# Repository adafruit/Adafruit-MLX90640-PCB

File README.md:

## Adafruit MLX90640 IR Thermal Camera Breakout PCB

<a href="http://www.adafruit.com/products/4407"><br/>
Click here to purchase one from the Adafruit shop</a><br/>
<a href="http://www.adafruit.com/products/4469"><br/>
Click here to purchase one from the Adafruit shop</a>

PCB files for the Adafruit MLX90640 IR Thermal Camera Breakout. 

Format is EagleCAD schematic and board layout
* https://www.adafruit.com/product/4407
* https://www.adafruit.com/product/4469

### Description

You can now add affordable heat-vision to your project and with an Adafruit MLX90640 Thermal Camera Breakout. This sensor contains a 24x32 array of IR thermal sensors. When connected to your microcontroller (or Raspberry Pi) it will return an array of 768 individual infrared temperature readings over I2C. It's like those fancy thermal cameras, but compact and simple enough for easy integration.

One version has a narrow 55°x35° field of view, and we also have a version with a wider 110°x70° field of view

This part will measure temperatures ranging from -40°C to 300°C with an accuracy of +- 2°C (in the 0-100°C range). With a maximum frame rate of 16 Hz (the theoretical limit is 32Hz but we were not able to practically achieve it), It's perfect for creating your own human detector or mini thermal camera. We have code for using this sensor on an Arduino or compatible (the sensor communicates over I2C) or on a Raspberry Pi with Python. If using an Arduino-compatible, you'll need a processor with at least 20KB RAM - a SAMD21 (M0) or SAMD51 (M4) chipset will do nicely. On the Pi, you can even perform interpolation processing with help from the SciPy python library and get some pretty nice results!

This sensor reads the data twice per frame, in a checker-board pattern, so it's normal to see a checker-board dither effect when moving the sensor around - the effect isn't noticeable when things move slowly.

To make it easy to use, we hand-soldered it on a breakout board with a 3.3V regulator and level shifting. So you can use it with any 3V or 5V microcontroller or computer. We've even included SparkFun qwiic compatible STEMMA QT connectors for the I2C bus so you don't even need to solder! Just plug-n-play with any of our STEMMA QT (JST SH) cables.

Even better - We've done all the hard work here, with example code and supporting software libraries to get you up in running in just a few lines of Arduino or Python code

### License

Adafruit invests time and resources providing this open source design, please support Adafruit and open-source hardware by purchasing products from [Adafruit](https://www.adafruit.com)!

Designed by Limor Fried/Ladyada for Adafruit Industries.

Creative Commons Attribution/Share-Alike, all text above must be included in any redistribution. 
See license.txt for additional details.

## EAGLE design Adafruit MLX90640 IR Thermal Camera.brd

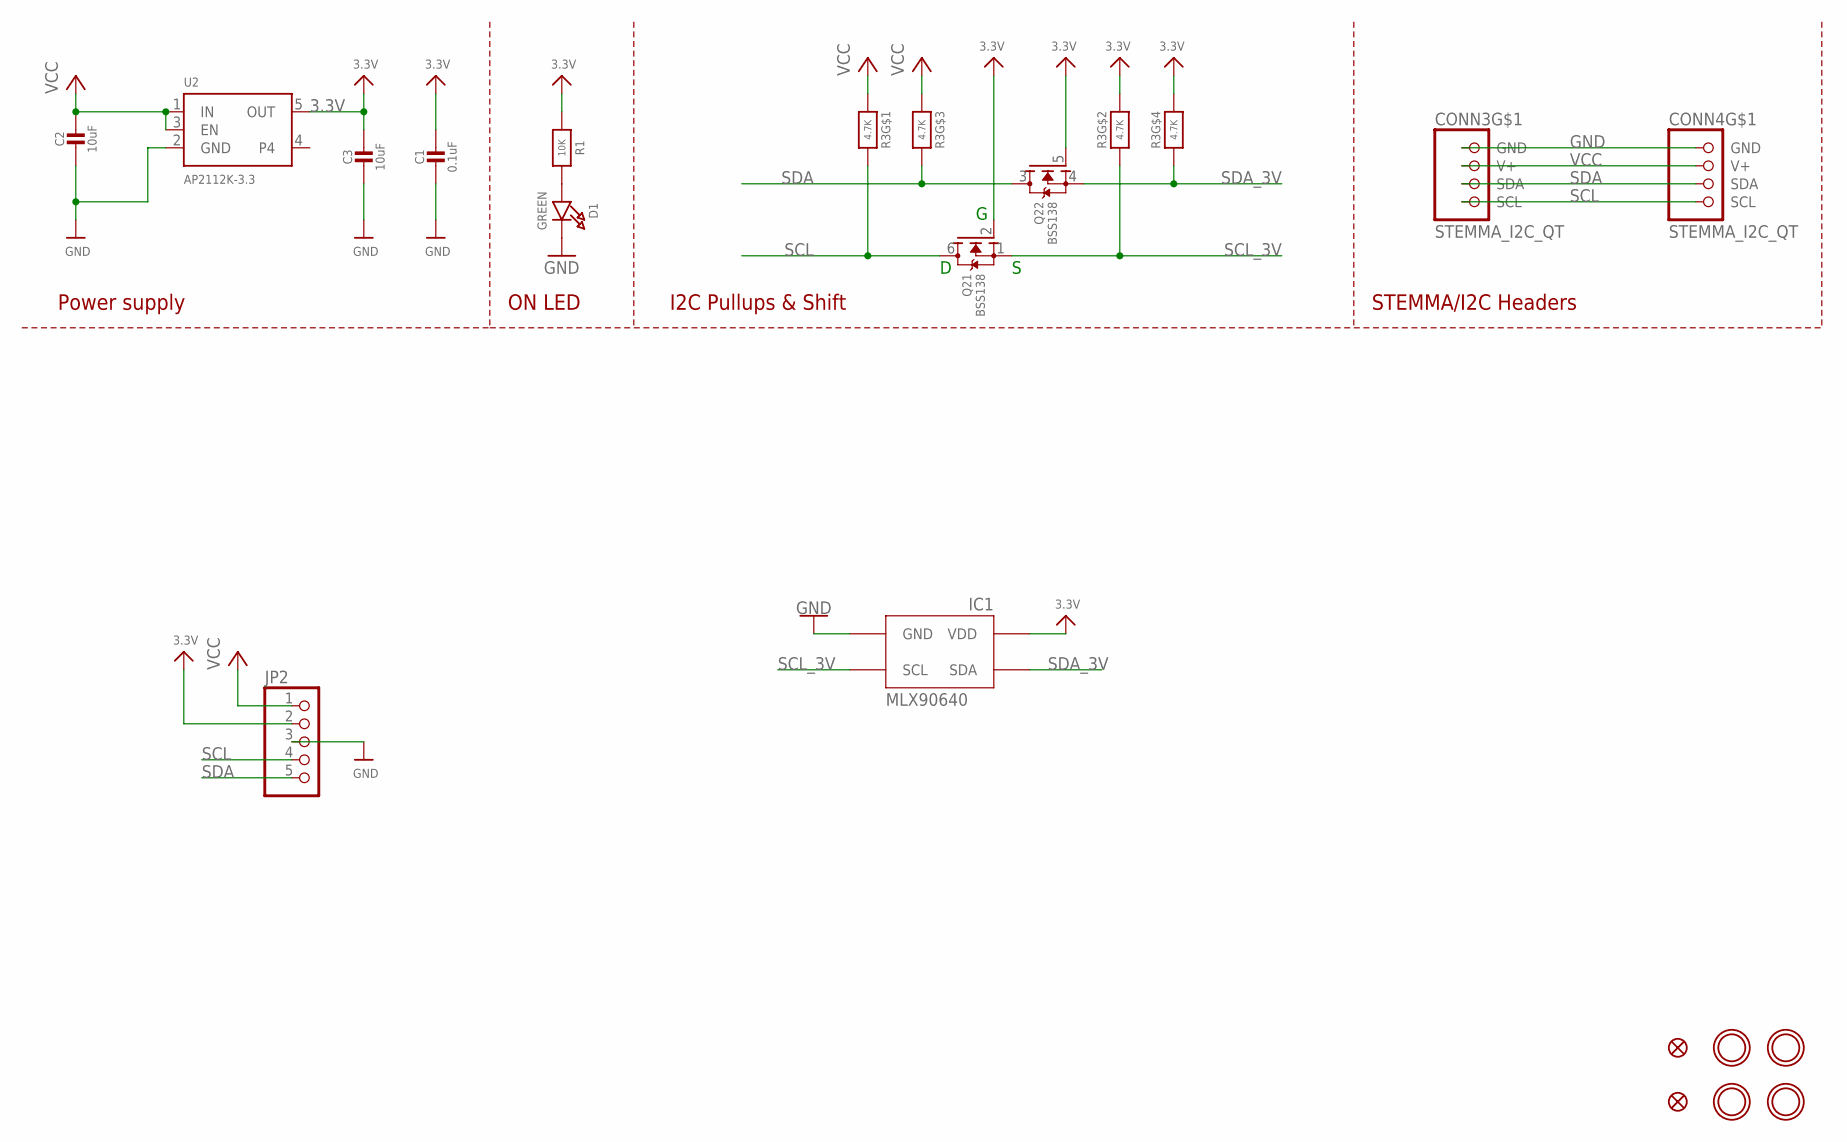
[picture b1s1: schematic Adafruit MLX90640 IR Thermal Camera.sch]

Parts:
C1: 0.1uF; 0603-NO
C2, C3: 10uF; 0805-NO
CONN3, CONN4: STEMMA_I2C_QT; JST_SH4
D1: GREEN; CHIPLED_0603_NOOUTLINE
FID3, FID4: FIDUCIAL_1MM
IC1: MLX90640
JP2: HEADER-1X5ROUND; 1X05_ROUND
Q2: BSS138; SOT363
R1: 10K; 0603-NO
R3: 4.7K; RESPACK_4X0603
U2: AP2112K-3.3; SOT23-5
U$1, U$17, U$19, U$21: MOUNTINGHOLE2.5; MOUNTINGHOLE_2.5_PLATED

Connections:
3.3V: C1.1, C3.1, IC1.VDD, JP2.2, Q2.2 (G), Q2.5 (G), R1.1, R3.2 (1), R3.4 (1), U2.5 (OUT)
GND: C1.2, C2.2, C3.2, CONN3.1 (GND), CONN4.1 (GND), D1.C, IC1.GND, JP2.3, U2.2 (GND)
unnamed: D1.A, R1.2
SCL: CONN3.4 (SCL), CONN4.4 (SCL), JP2.4, Q2.6 (D), R3.8 (2)
SCL_3V: IC1.SCL, Q2.1 (S), R3.7 (2)
SDA: CONN3.3 (SDA), CONN4.3 (SDA), JP2.5, Q2.3 (D), R3.6 (2)
SDA_3V: IC1.SDA, Q2.4 (S), R3.5 (2)
VCC: C2.1, CONN3.2 (V+), CONN4.2 (V+), JP2.1, R3.1, R3.3 (1), U2.1 (IN), U2.3 (EN)

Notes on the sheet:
I2C Pullups & Shift
STEMMA/I2C Headers
ON LED
Power supply

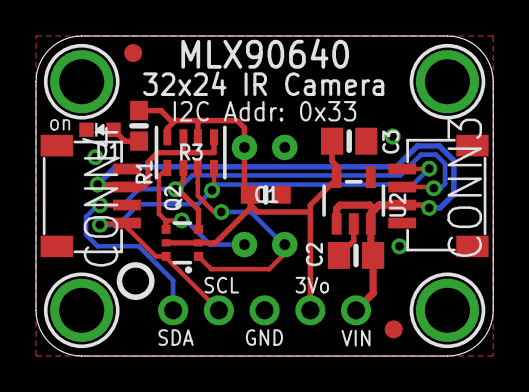
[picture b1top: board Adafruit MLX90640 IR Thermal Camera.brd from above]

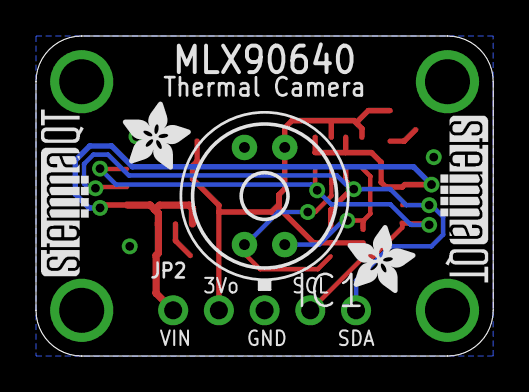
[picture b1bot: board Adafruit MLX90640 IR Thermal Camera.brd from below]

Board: 2 copper layers, 25.4 x 17.8 mm, 23 parts (6 on the bottom side), 8 nets.

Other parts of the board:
U$4, U$22: ADAFRUIT_3.5MM
U$25: PCBFEAT-REV-040
U$30, U$31: STEMMAQT

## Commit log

2020-01-24 Adding board files.
2020-01-24 Add break.

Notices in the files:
parts and their libraries:
microbuilder: This work is placed in the public domain, and may be freely used for commercial and non-commercial work with the following conditions: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
SparkFun-PowerSymbols: Licensing: Creative Commons ShareAlike 4.0 International - https://creativecommons.org/licenses/by-sa/4.0
